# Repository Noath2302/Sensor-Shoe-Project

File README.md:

# Sensor-Shoe-Project
Sensor-Shoe Project FRA-UAS 2019 VGU EEIT2015 Truong Thanh Toan
Deadline around 18-20/08

25/06/2019
-- Create a github repository

Work to do:
-- Make the full PCB for testing
-- Optimize the usage of sensor system
-- Adding also the thesis to the repository

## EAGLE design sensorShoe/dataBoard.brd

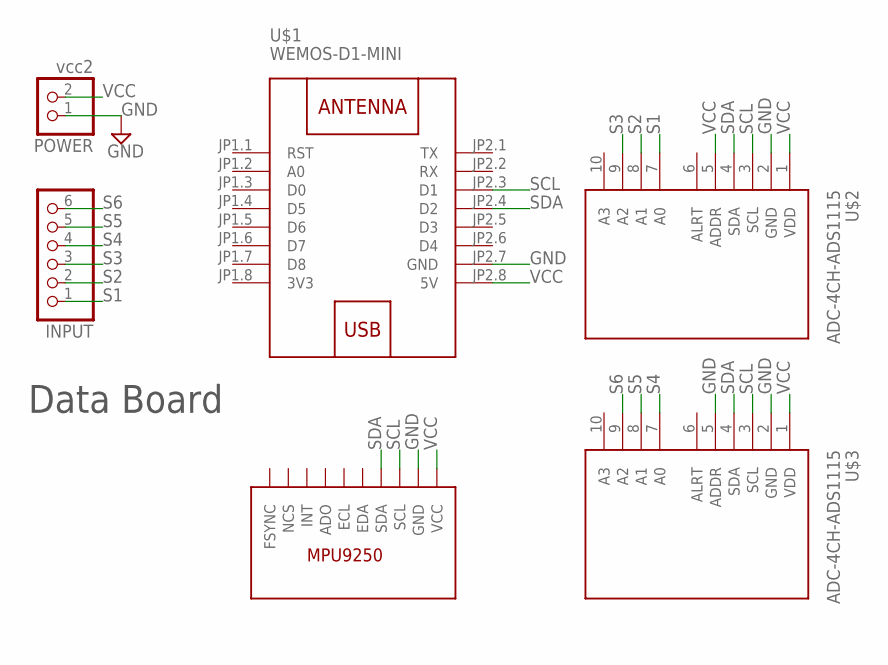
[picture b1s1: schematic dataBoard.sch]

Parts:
INPUT: PINHD-1X6; 1X06
MPU1: MPU9250
POWER: vcc2; 1X02
U$1: WEMOS-D1-MINI
U$2, U$3: ADC-4CH-ADS1115

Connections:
3V3: U$1.JP1.8 (3V3)
GND: MPU1.GND, POWER.1, U$1.JP2.7 (GND), U$2.2 (GND), U$3.2 (GND), U$3.5 (ADDR)
S1: INPUT.1, U$2.7 (A0)
S2: INPUT.2, U$2.8 (A1)
S3: INPUT.3, U$2.9 (A2)
S4: INPUT.4, U$3.7 (A0)
S5: INPUT.5, U$3.8 (A1)
S6: INPUT.6, U$3.9 (A2)
SCL: MPU1.SCL, U$1.JP2.3 (D1), U$2.3 (SCL), U$3.3 (SCL)
SDA: MPU1.SDA, U$1.JP2.4 (D2), U$2.4 (SDA), U$3.4 (SDA)
VCC: MPU1.VCC, POWER.2, U$1.JP2.8 (5V), U$2.1 (VDD), U$2.5 (ADDR), U$3.1 (VDD)

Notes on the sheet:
Data Board

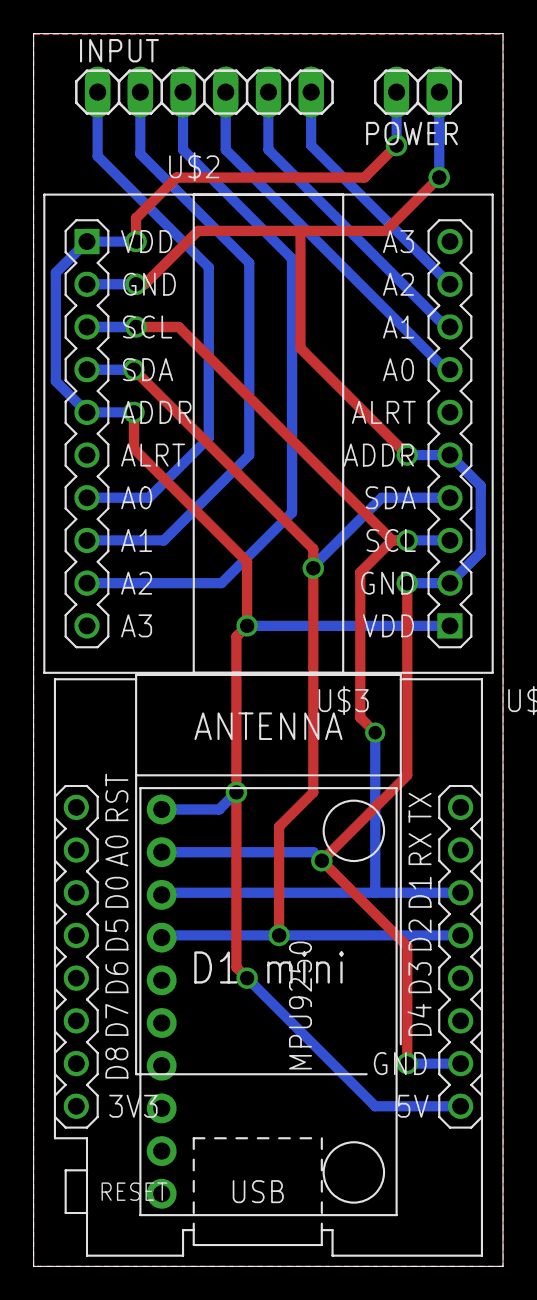
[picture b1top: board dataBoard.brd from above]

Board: 2 copper layers, 27.9 x 73.3 mm, 6 parts (0 on the bottom side), 10 nets.

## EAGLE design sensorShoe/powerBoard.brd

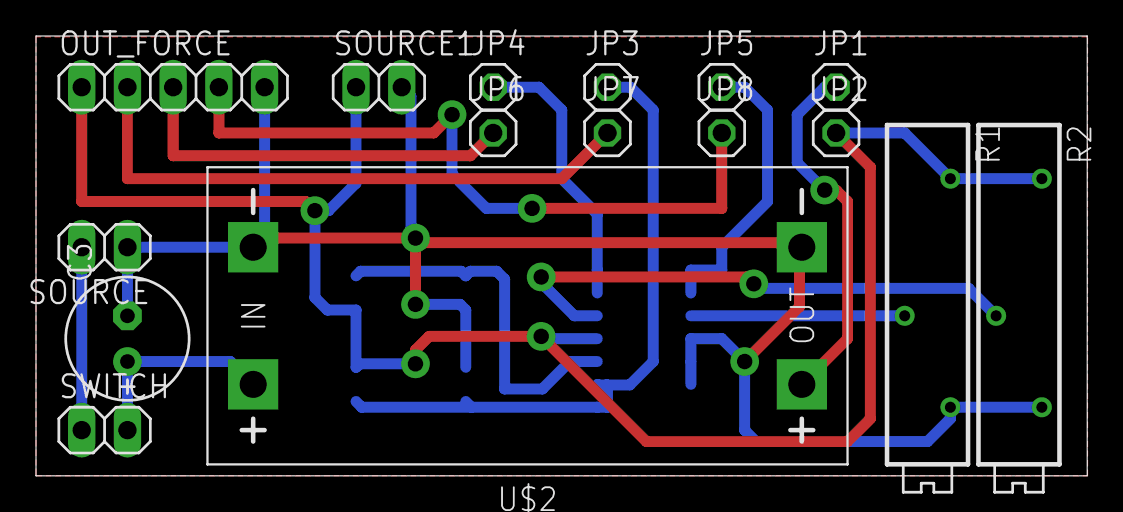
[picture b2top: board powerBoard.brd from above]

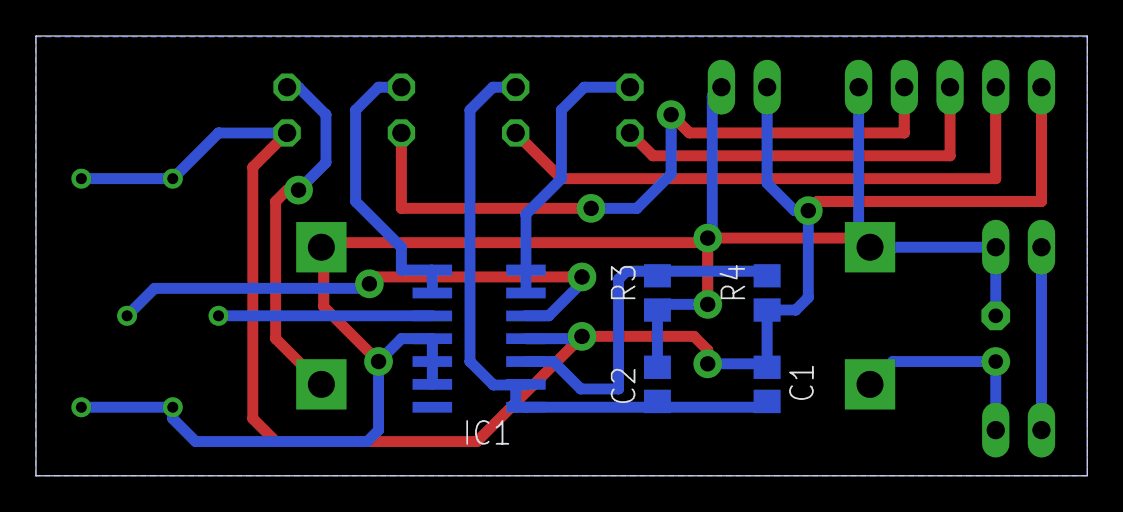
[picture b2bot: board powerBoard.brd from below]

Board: 2 copper layers, 58.4 x 24.4 mm, 21 parts (5 on the bottom side), 14 nets.

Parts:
C1, C2: 47uF; C0805
C3: 470uF; E2,5-7
IC1: LMV324M; SO14
JP1, JP2, JP3, JP4, JP5, JP6, JP7, JP8: 1X01
OUT_FORCE: 1X05
R1, R2: 100k; RTRIM3006P
R3, R4: 10k; R0805
SOURCE, SOURCE1: 1X02
SWITCH: 1X02
U$2: DC-DC-STEP-UP-MT3608

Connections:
GND: C2.2, C3.-, IC1.11, IC1.12, IC1.13, OUT_FORCE.5, R1.3, R2.3, R3.1, SOURCE.1, SOURCE1.2, U$2.IN-, U$2.OUT-
unnamed: JP1.1, U$2.OUT+
unnamed: IC1.3, R3.2, R4.2
unnamed: SOURCE.2, SWITCH.1
unnamed: C3.+, SWITCH.2, U$2.IN+
unnamed: IC1.5, R2.2
unnamed: IC1.10, R1.2
unnamed: JP8.1, OUT_FORCE.4
unnamed: JP6.1, OUT_FORCE.3
unnamed: JP7.1, OUT_FORCE.2
VG: C1.2, C2.1, IC1.1, IC1.2, JP3.1
VG-1: IC1.8, IC1.9, JP5.1
VG/2: IC1.6, IC1.7, JP4.1
VHIGH: C1.1, IC1.4, JP2.1, OUT_FORCE.1, R1.1, R2.1, R4.1, SOURCE1.1

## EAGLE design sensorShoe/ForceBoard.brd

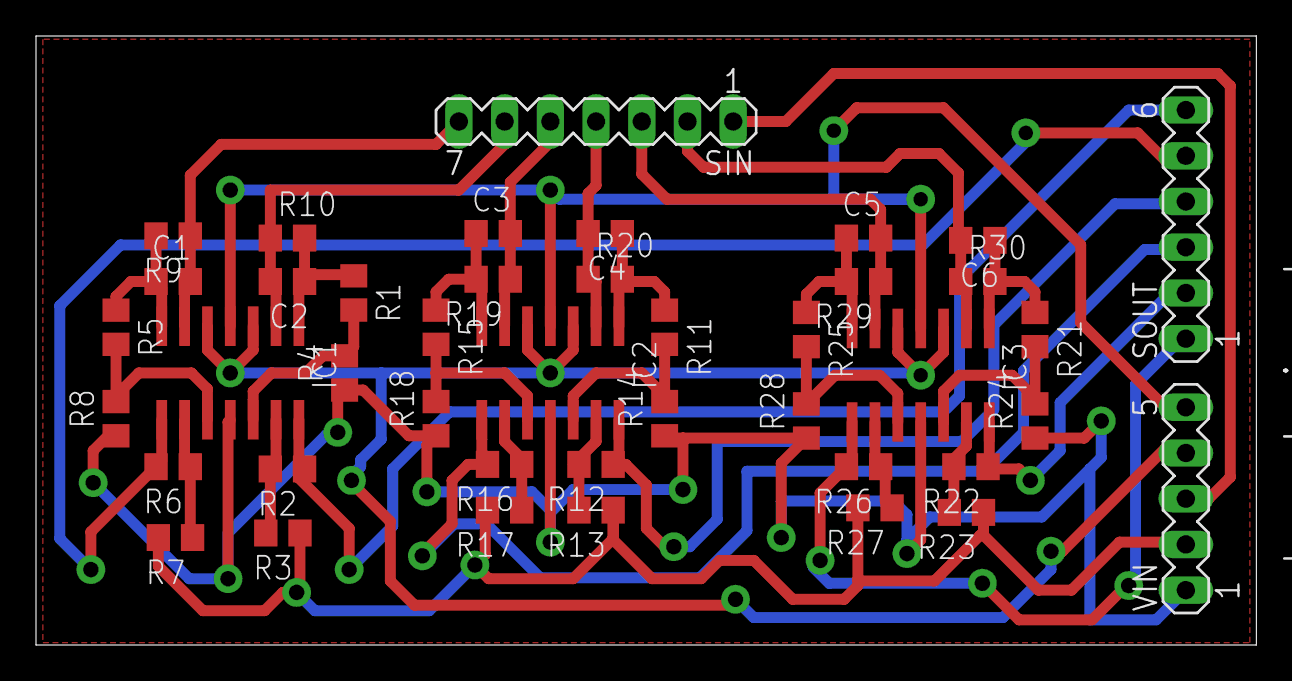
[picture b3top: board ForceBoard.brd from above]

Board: 2 copper layers, 67.8 x 33.8 mm, 42 parts (0 on the bottom side), 35 nets.

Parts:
C1, C2, C3, C4, C5, C6: 47pF; C0805
IC1, IC2, IC3: LMV324M; SO14
R1, R2, R3, R4, R5, R6, R7, R8, R11, R12, R13, R14, R15, R16, R17, R18, R21, R22, R23, R24, R25, R26, R27, R28: 330; R0805
R9, R10, R19, R20, R29, R30: 100k; R0805
SIN: Sensor input; MA07-1
SOUT: Board Output; MA06-1
VIN: Input voltage; MA05-1

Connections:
GND: IC1.11, IC2.11, IC3.11, R4.1, R8.1, R14.1, R18.1, R24.1, R28.1, VIN.1
unnamed: IC2.13, R12.2, R13.2
unnamed: IC1.10, R5.2, R8.2
unnamed: IC1.13, R2.2, R3.2
unnamed: C1.1, IC1.7, R5.1, R9.2
unnamed: IC1.9, R6.1, R7.1
unnamed: IC1.12, R1.2, R4.2
unnamed: C3.1, IC2.7, R15.1, R19.2
unnamed: IC2.9, R16.1, R17.1
unnamed: C2.1, IC1.1, R1.1, R10.2
unnamed: IC2.10, R15.2, R18.2
unnamed: IC2.12, R11.2, R14.2
unnamed: C4.1, IC2.1, R11.1, R20.2
unnamed: IC3.13, R22.2, R23.2
unnamed: C5.1, IC3.7, R25.1, R29.2
unnamed: IC3.9, R26.1, R27.1
unnamed: IC3.10, R25.2, R28.2
unnamed: IC3.12, R21.2, R24.2
unnamed: C6.1, IC3.1, R21.1, R30.2
S1: IC1.14, R2.1, SOUT.6
S1IN: C2.2, IC1.2, R10.1, SIN.6
S2: IC1.8, R6.2, SOUT.5
S2IN: C1.2, IC1.6, R9.1, SIN.7
S3: IC2.14, R12.1, SOUT.4
S3IN: C4.2, IC2.2, R20.1, SIN.4
S4: IC2.8, R16.2, SOUT.3
S4IN: C3.2, IC2.6, R19.1, SIN.5
S5: IC3.14, R22.1, SOUT.2
S5IN: C6.2, IC3.2, R30.1, SIN.2
S6: IC3.8, R26.2, SOUT.1
S6IN: C5.2, IC3.6, R29.1, SIN.3
VG: IC1.3, IC1.5, IC2.3, IC2.5, IC3.3, IC3.5, VIN.4
VG-1: R3.1, R7.2, R13.1, R17.2, R23.1, R27.2, VIN.2
VG/2: SIN.1, VIN.3
VHIGH: IC1.4, IC2.4, IC3.4, VIN.5

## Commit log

2019-06-25 initialize the repository
2019-06-25 add shoe_5 current board design
2019-07-01 please do more wiring
2019-07-18 checking day 18/07
2019-07-18 checking day 18/07 - Eagle board update
2019-11-06 adding license

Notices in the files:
parts and their libraries:
diy-modules: Released under the Creative Commons Attribution 4.0 International License: http://creativecommons.org/licenses/by/4.0
